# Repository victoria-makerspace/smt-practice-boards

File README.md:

# SMT Practice Boards

This repository contains Surface Mount Technology(SMT) board designs that are intended to be used for training purposes.  Every SMT practice board design provides the information:  

1. bom:  Bill of Materials, including DigiKey part references.
1. gerber: files used to order PCBs from suppliers such as PCBWay or JLCPCB.
1. images:  photos of the board
1. kicad:  KiCAD schematic and layout files.  Fiducials are included on the layouts to support automatic pick and place machines.
1. schematic:  PDF schematic 
1. stencil:  DXF and LightBurn format files used to make laser cut stencils.  Laser cut stencils can be created using 4 mil mylar. 

## Rotating LEDs Practice Board
The [Rotating LEDs practice board](https://github.com/victoria-makerspace/smt-practice-boards/tree/main/board-rotating-leds) is inspired from the [Gikfun SMT training board](https://gikfun.com/collections/frontpage/products/gikfun-diy-smd-smt-welding-practice-soldering-skill-training-board)

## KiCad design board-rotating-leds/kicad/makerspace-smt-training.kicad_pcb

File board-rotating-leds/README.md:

# Rotating LEDs Practice Board

Click on the image below to see the demo

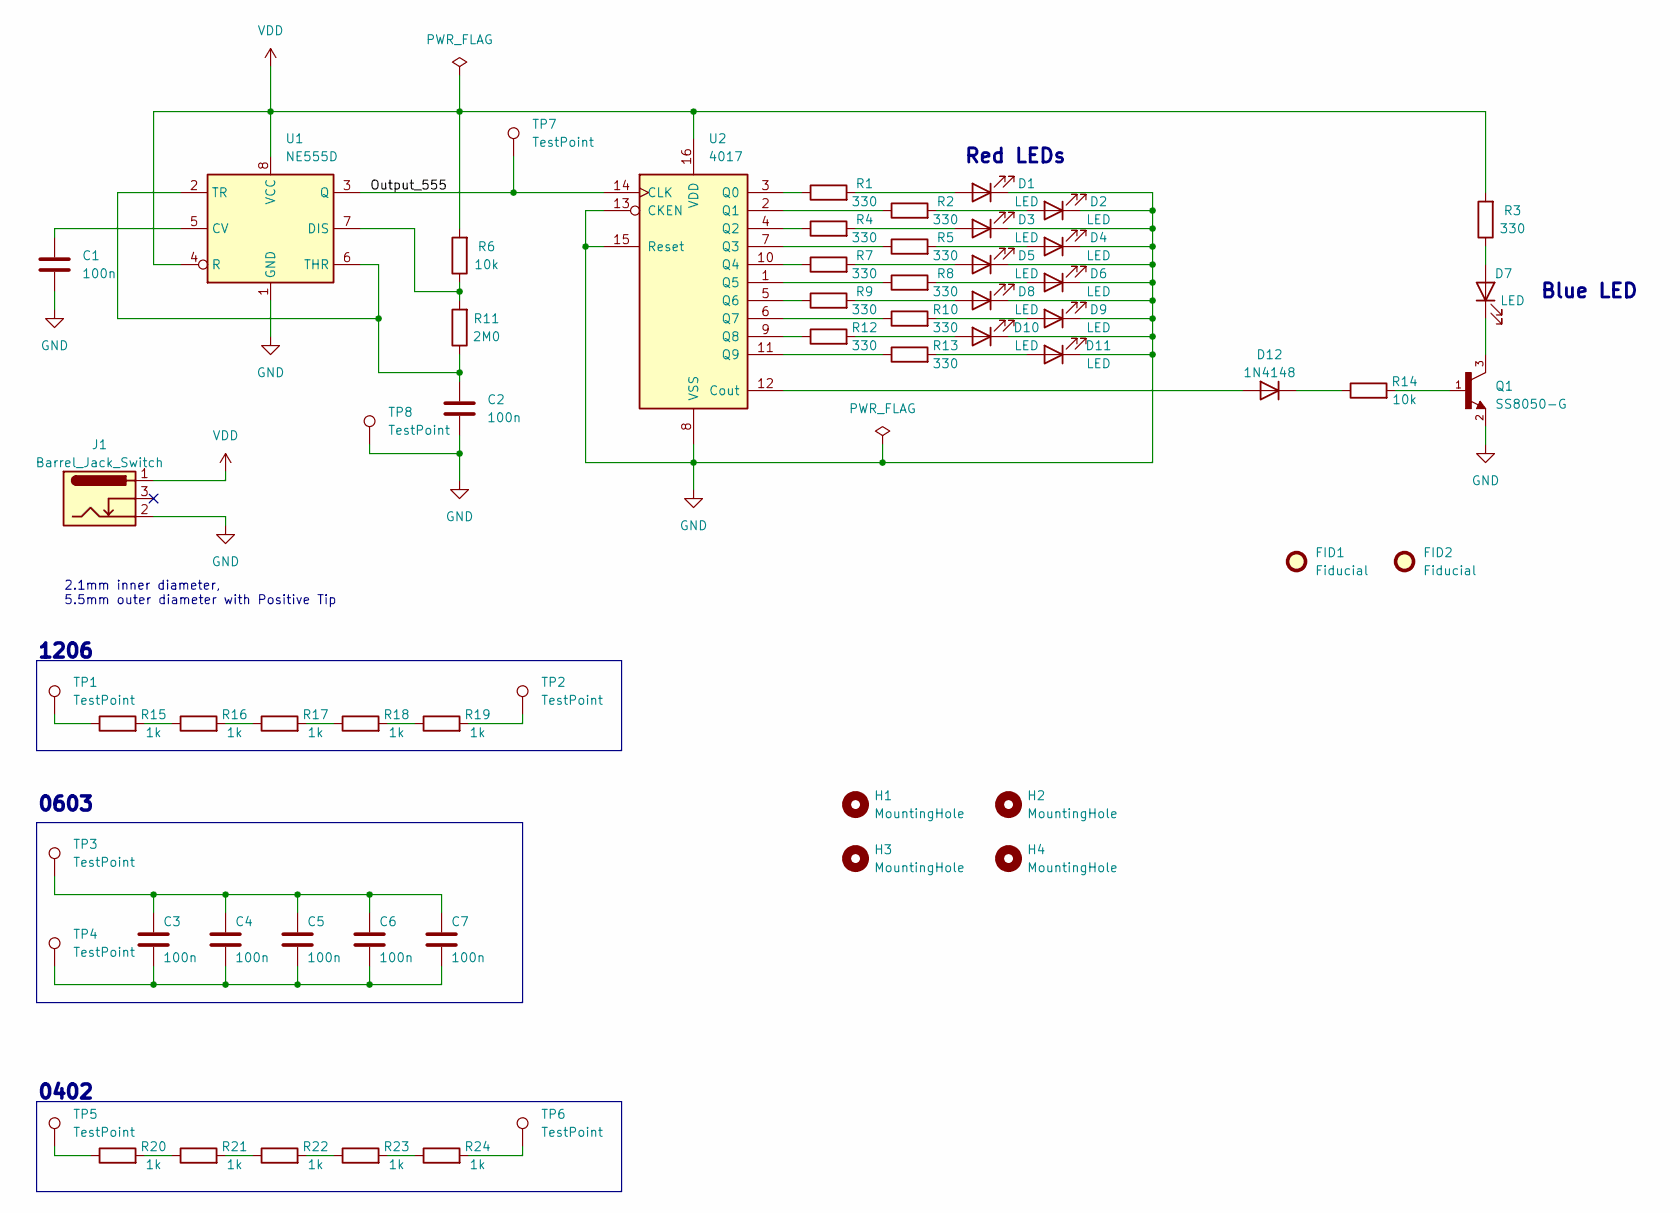
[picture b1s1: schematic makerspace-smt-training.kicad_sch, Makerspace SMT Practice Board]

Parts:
C1: 100n
C2: 100n; C_0805_2012Metric
C3, C4, C5, C6, C7: 100n; C_0603_1608Metric
D1, D2, D3, D4, D5, D6, D7, D8, D9, D10, D11: LED; LED_0805_2012Metric
D12: 1N4148; D_SOD-123
FID1, FID2: Fiducial; Fiducial_1.5mm_Mask3mm
H1, H2, H3, H4: MountingHole; MountingHole_3.2mm_M3
J1: Barrel_Jack_Switch; BarrelJack_GCT_DCJ200-10-A_Horizontal
Q1: SS8050-G; TRANS_SS8050-G; PARTREV A
R1, R2, R3, R4, R5, R7, R8, R9, R10, R12, R13: 330; R_0805_2012Metric
R6, R14: 10k; R_0805_2012Metric
R11: 2M0; R_0805_2012Metric
R15, R16, R17, R18, R19: 1k; R_1206_3216Metric
R20, R21, R22, R23, R24: 1k; R_0402_1005Metric
TP1, TP2, TP3, TP4, TP5, TP6: TestPoint; TestPoint_Pad_D1.5mm
TP7, TP8: TestPoint; TestPoint_Loop_D1.80mm_Drill1.0mm_Beaded
U1: NE555D; SOIC-8_3.9x4.9mm_P1.27mm
U2: 4017; SOIC-16_3.9x9.9mm_P1.27mm

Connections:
/Output_555: TP7.1, U1.3 (Q), U2.14 (CLK)
GND: C1.2, C2.2, D1.1 (K), D2.1 (K), D3.1 (K), D4.1 (K), D5.1 (K), D6.1 (K), D8.1 (K), D9.1 (K), D10.1 (K), D11.1 (K), J1.2, Q1.2, TP8.1, U1.1 (GND), U2.8 (VSS), U2.13 (CKEN), U2.15 (Reset)
unnamed: C3.1, C4.1, C5.1, C6.1, C7.1, TP3.1
unnamed: C3.2, C4.2, C5.2, C6.2, C7.2, TP4.1
unnamed: D1.2 (A), R1.2
unnamed: D2.2 (A), R2.2
unnamed: D3.2 (A), R4.2
unnamed: D4.2 (A), R5.2
unnamed: D5.2 (A), R7.2
unnamed: D6.2 (A), R8.2
unnamed: D7.2 (A), R3.1
unnamed: D7.1 (K), Q1.3
unnamed: D8.2 (A), R9.2
unnamed: D9.2 (A), R10.2
unnamed: D10.2 (A), R12.2
unnamed: D11.2 (A), R13.2
unnamed: D12.2 (A), U2.12 (Cout)
unnamed: D12.1 (K), R14.1
unnamed: Q1.1, R14.2
unnamed: R15.1, TP1.1
unnamed: R15.2, R16.1
unnamed: R16.2, R17.1
unnamed: R17.2, R18.1
unnamed: R18.2, R19.1
unnamed: R19.2, TP2.1
unnamed: R20.1, TP5.1
unnamed: R20.2, R21.1
unnamed: R21.2, R22.1
unnamed: R22.2, R23.1
unnamed: R23.2, R24.1
unnamed: R24.2, TP6.1
unnamed: C1.1, U1.5 (CV)
unnamed: R6.1, R11.2, U1.7 (DIS)
unnamed: C2.1, R11.1, U1.2 (TR), U1.6 (THR)
unnamed: R1.1, U2.3 (Q0)
unnamed: R2.1, U2.2 (Q1)
unnamed: R4.1, U2.4 (Q2)
unnamed: R5.1, U2.7 (Q3)
unnamed: R7.1, U2.10 (Q4)
unnamed: R8.1, U2.1 (Q5)
unnamed: R9.1, U2.5 (Q6)
unnamed: R10.1, U2.6 (Q7)
unnamed: R12.1, U2.9 (Q8)
unnamed: R13.1, U2.11 (Q9)
VDD: J1.1, R3.2, R6.2, U1.4 (R), U1.8 (VCC), U2.16 (VDD)

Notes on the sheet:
0603
2.1mm inner diameter, 5.5mm outer diameter with Positive Tip
1206
Blue LED
0402
Red LEDs

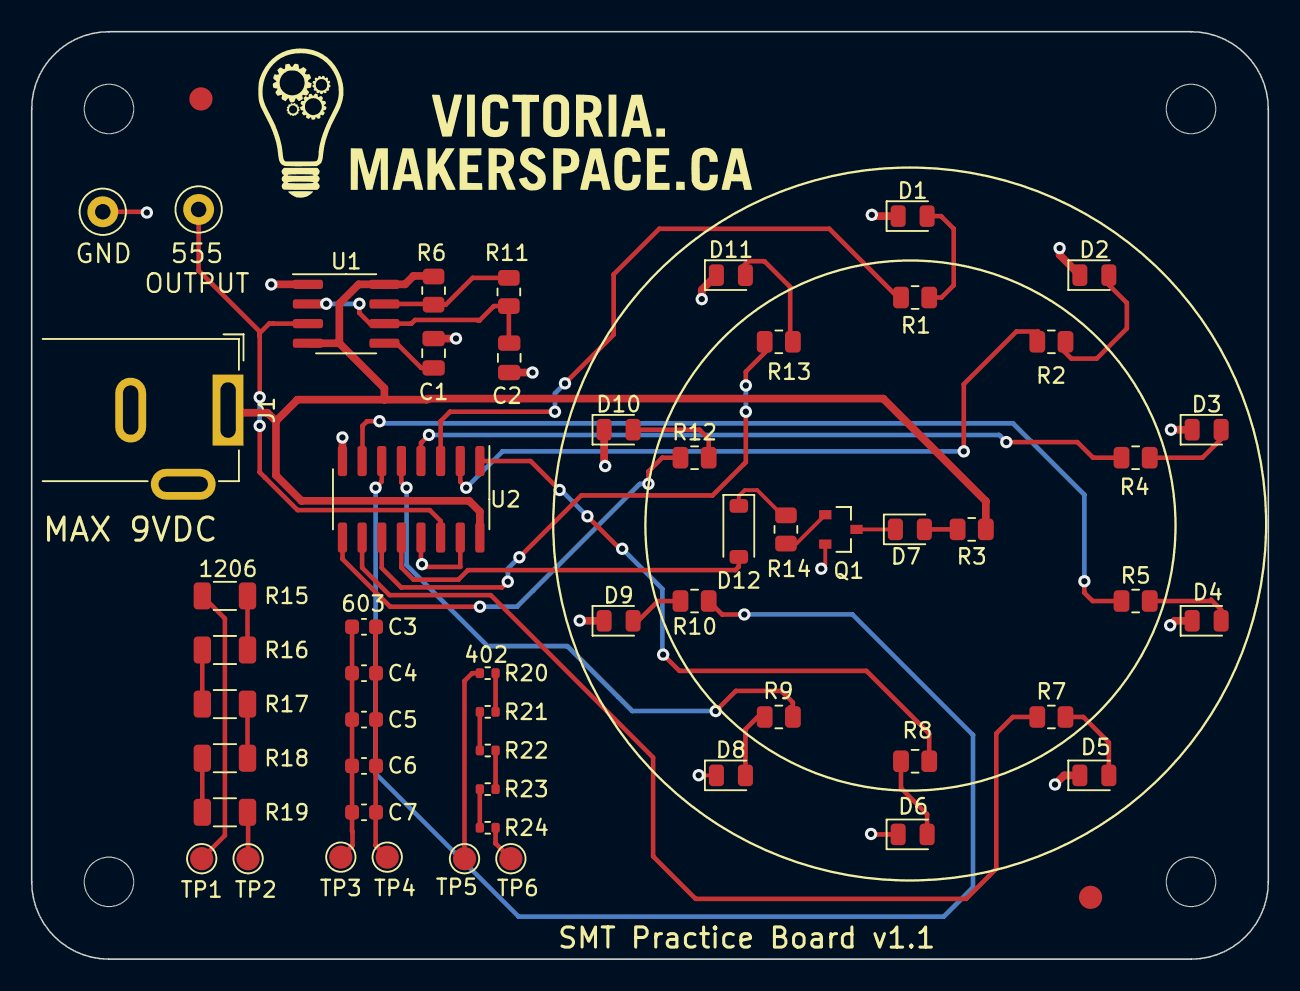
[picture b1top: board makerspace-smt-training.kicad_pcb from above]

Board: 2 copper layers, 80.0 x 60.0 mm, 61 parts (0 on the bottom side), 45 nets.

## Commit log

2023-08-31 version 1.1 of Rotating LED SMT practice board
2023-08-31 Update README.md
    added video showing the board in action
2023-08-31 added BOM
